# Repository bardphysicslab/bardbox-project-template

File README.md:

# bardbox-project-template

`bardbox-project-template` is the BardBox reference implementation and GitHub
template repo. New monitor projects should be created from this repo.

The canonical standards live in the separate `bardbox` repo. This template
implements those standards in working code: FastAPI backend, example driver,
dark BardBox dashboard, scripts, docs, and tests. Current firmware development
and proving live in [BardBox-Reference](https://github.com/bardphysicslab/BardBox-Reference/tree/main/software/firmware); this template intentionally contains no firmware copy.

## Decision history and contribution workflow

See the [implementation decision index](docs/DECISIONS.md), which links shared
platform reasoning back to BardBox. Use the issue and pull-request prompts with
the [shared development workflow](https://github.com/bardphysicslab/engineering-standards/blob/main/development-workflow.md).
Routine fixes stay brief; shared specifications are not copied into this template.

## Repo Roles

`bardbox` is the standards/specification repo.

`bardbox-project-template` is the reference implementation/template repo.

Workflow:

1. Protocol or UI rule changes are documented first in `bardbox`.
2. New capabilities are developed and proven in `BardBox-Reference` first,
   then verified reusable implementation, tests and build/configuration guidance
   are promoted into `bardbox-project-template` as tracked completion work
   ([TEMPLATE-PROVING-1](https://github.com/bardphysicslab/bardbox-project-template/issues/31#issuecomment-6281614801)).
   After promotion, Reference consumes the maintained implementation through the
   reviewed dependency boundary and retains its example configuration/demos.
3. New monitor repos are created from `bardbox-project-template`.
4. Existing monitor repos like GoLab, RKC, Solar, and CESH Air should be updated from the template standard when practical.
5. Project-specific repos should not invent protocol behavior unless it is promoted back into `bardbox` and `bardbox-project-template`.

Goal: one documented standard, one reference implementation, many project instances.

## What This Template Provides

- FastAPI Raspberry Pi app
- normalized reading API
- node freshness handling with `ok`, `stale`, `error`, and `node_unavailable`
- current node UID examples using `bb-<site>-<type>-<instance>`
- example driver contract
- CESH Air/RKC-derived BardBox landing and detail layouts
- reusable cards, status badges, foldouts, table, chart container, and mobile CSS
- exact lightweight `/health` endpoint and two-layer systemd/watchdog examples
- optional fail-closed read-only historical Data API
- canonical safe configuration synchronizer
- conditional verified-backup guidance and Tailscale deployment checklist
- root `bardbox.toml` project/service/config metadata for shared BardBox tooling
- isolated Python 3.12 development environment
- Dev Container and GitHub Actions test environment
- links to the current firmware proving home in Reference
- tests for stale/unavailable behavior

## Development Setup

Each BardBox repository owns its own Python environment. Do not run this project
from another BardBox repository's `.venv`; dependency leakage between repos can
hide or create failures that are not reproducible elsewhere.

From the repository root:

```bash
python3.12 -m venv .venv
source .venv/bin/activate
python -m pip install --upgrade pip
python -m pip install -r requirements-dev.txt
python -m pytest
```

Runtime dependencies remain in `requirements.txt`; development/test additions
are in `requirements-dev.txt`.

The repository includes a Python 3.12 Dev Container. With Docker running, validate
an identified committed revision in a fresh Linux container:

```bash
bash scripts/validate_container.sh HEAD
```

The runner prints the source commit, image identity/platform, interpreter and
resolved package versions. It builds from committed `.devcontainer` files and
streams a committed source archive into temporary container storage. Local edits,
untracked files and host virtual environments are excluded; commit intended changes
before using this as validation evidence. No host credentials, socket or hardware
are mounted. Dependencies require network access; fixture tests do not require
production devices. Containers are removed on exit; build images/cache remain for
reuse. This validates the native Docker architecture, not all CPU architectures.

CI runs the same command alongside isolated Python tests. The image tag and some
dependency ranges can resolve differently later; retain the printed evidence for
release reproducibility. Production Pi services continue to run natively/systemd.

A template change should pass both the repository's isolated local environment
and the clean Linux container before it is treated as a portable BardBox
foundation change.

## Quick Start

With the repository's `.venv` active:

```bash
uvicorn software.app.main:app --reload
```

Open [http://127.0.0.1:8000](http://127.0.0.1:8000). The landing page links to
the reference detail dashboard at `/monitor`.

Run commands from the repo root. The `software/app/` folder is a Python package;
do not `cd software/app` and run `uvicorn main:app`.

## First Customizations

1. Edit the root `bardbox.toml` project and service metadata.
2. Edit `software/app/config/app_config.example.json`.
3. Replace or add drivers under `software/app/drivers/`.
4. Follow [Reference firmware](https://github.com/bardphysicslab/BardBox-Reference/tree/main/software/firmware) for device development/proving; do not create a second firmware copy here.
5. Adjust dashboard labels and metric choices while preserving BardBox status/null behavior.
6. Add project-specific docs under `docs/`.

New node UIDs must use `bb-<site>-<type>-<instance>`, for example
`bb-prj-air-001`. Legacy `bb-0001` style IDs remain supported for existing
deployments but are deprecated.

During migration, add `legacy_uids` to a driver config to accept old
device-reported IDs while normalizing API/dashboard output to the canonical UID.
Historical logs are not rewritten.

## Firmware

Current firmware source, build definitions, host tests and demo receiver live in
[BardBox-Reference](https://github.com/bardphysicslab/BardBox-Reference/tree/main/software/firmware). The duplicate tree and firmware-only support were
[removed at Kornelis's request](https://github.com/bardphysicslab/bardbox-project-template/issues/36#issuecomment-6315599802); Template retains its server app and
normalized diagnostic receiver. Reference firmware is still under testing and
cleanup; this pointer does not claim a complete promoted firmware template.
Later reusable promotion/packaging is tracked in [#36](https://github.com/bardphysicslab/bardbox-project-template/issues/36).
Firmware uses VS Code + PlatformIO in Reference; no firmware build is run here.

## Repository Layout

```text
project/
├── bardbox.toml
├── .devcontainer/
├── .github/workflows/
├── software/
│   └── app/
├── hardware/
│   ├── ecad/
│   └── mcad/
├── data/
├── deploy/
├── docs/
├── scripts/
├── tests/
├── requirements.txt
├── requirements-dev.txt
└── README.md
```

## Standards Reference

Use `bardbox` as the specification repo for protocol, reading format, driver
boundaries, UI standards, channel names, and design decisions.
Network-uploading firmware must follow the canonical
[BardBox Web Node Protocol](https://github.com/bardphysicslab/bardbox/blob/main/docs/web-node-protocol.md);
this template keeps only a concise implementation checklist in
`docs/device-instructions.md`.

## BardBox Operations

After every source update, check whether the ignored live configuration needs
migration. Check mode performs no writes and exits non-zero if additions are
pending:

```bash
python3 scripts/sync_app_config.py --check
```

An informational preview is also available as either
`python3 scripts/sync_app_config.py` or
`python3 scripts/sync_app_config.py --dry-run`.

Apply the reviewed merge with:

```bash
python3 scripts/sync_app_config.py --write
```

The canonical BardBox synchronizer recursively adds new example fields while
preserving deployment values, secrets, and unknown local fields.
It matches nodes by UID, preserves local-only nodes, and does not automatically
create example-only nodes. Apply mode first creates a timestamped backup and
then atomically replaces the live file.

A deployment is ready to restart only when the check reports:

```text
Added keys: none
Added node fields: none
```

The deployment sequence is: pull, check, review/apply additions, check again,
restart, verify `/health`, and smoke-test the application.

`software/app/config/app_config.example.json` is sanitized and version
controlled. Copy it to ignored `software/app/config/app_config.json` for local
or production deployment values. Never place real secrets in the example.

## Availability Standard

Every deployed FastAPI/Uvicorn service needs both layers in `deploy/`:

- `Restart=always` and `RestartSec=5` recover an exited process;
- the one-minute watchdog checks `GET /health` and restarts after three
  consecutive failures, recovering a live but unresponsive process.

Adapt the generic paths, user, port, and service name before installation. Keep
the watchdog generic; do not add sensor or alert logic.

## Conditional Data API

The canonical router is included but disabled by default. It is appropriate only
when the deployment owns a clean `data/readings/` archive. Configure a dedicated
token only in ignored `app_config.json`:

```json
"data_api": { "token": "<dedicated read-only token>" }
```

An empty token fails closed. Authenticated consumers such as `bardbox-mcp` use
`GET /api/data/files` and `GET /api/data/files/{path}`. The API exposes only
CSV/CSV.GZ files and performs no writes, administration, or analysis. Remove or
leave the router disabled when a project has no suitable readings root.

## Optional Backup

Projects that retain and later prune local history should adapt the proven CESH
Air verified-manifest lifecycle. See `docs/backup-reference.md`. Stateless
projects should not add backup machinery.

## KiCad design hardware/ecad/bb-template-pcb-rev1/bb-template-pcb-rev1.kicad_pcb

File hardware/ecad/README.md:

# ECAD

Store version-controlled electronic design files, schematics, PCB layouts, and
related fabrication documentation for the project here.

The BardBox PCB template is forthcoming. The earlier draft
(`bb-template-pcb-rev1`) was removed from the active tree on October 20, 2026,
and remains in Git history.

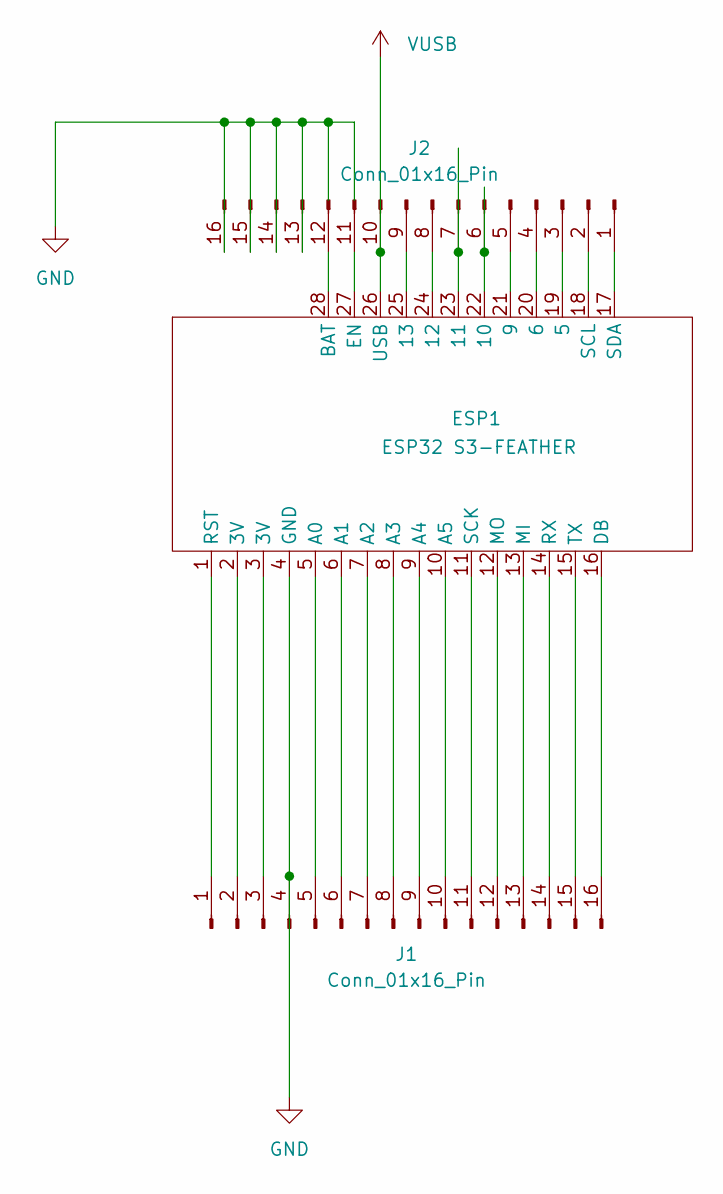
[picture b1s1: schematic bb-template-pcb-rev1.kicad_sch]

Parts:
ESP1: ESP32 S3-FEATHER
J1, J2: Conn_01x16_Pin; PinHeader_1x16_P2.54mm_Vertical

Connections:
GND: ESP1.4 (GND), J1.4, J2.13, J2.14, J2.15, J2.16
unnamed: ESP1.19 (5), J2.3
unnamed: ESP1.20 (6), J2.4
unnamed: ESP1.21 (9), J2.5
unnamed: ESP1.22 (10), J2.6
unnamed: ESP1.23 (11), J2.7
unnamed: ESP1.24 (12), J2.8
unnamed: ESP1.25 (13), J2.9
unnamed: ESP1.5 (A0), J1.5
unnamed: ESP1.6 (A1), J1.6
unnamed: ESP1.7 (A2), J1.7
unnamed: ESP1.8 (A3), J1.8
unnamed: ESP1.9 (A4), J1.9
unnamed: ESP1.10 (A5), J1.10
unnamed: ESP1.28 (BAT), J2.12
unnamed: ESP1.16 (DB), J1.16
unnamed: ESP1.27 (EN), J2.11
unnamed: ESP1.13 (MI), J1.13
unnamed: ESP1.12 (MO), J1.12
unnamed: ESP1.1 (RST), J1.1
unnamed: ESP1.14 (RX), J1.14
unnamed: ESP1.11 (SCK), J1.11
unnamed: ESP1.18 (SCL), J2.2
unnamed: ESP1.17 (SDA), J2.1
unnamed: ESP1.15 (TX), J1.15
unnamed: ESP1.2 (3V), J1.2
unnamed: ESP1.3 (3V), J1.3
VUSB: ESP1.26 (USB), J2.10

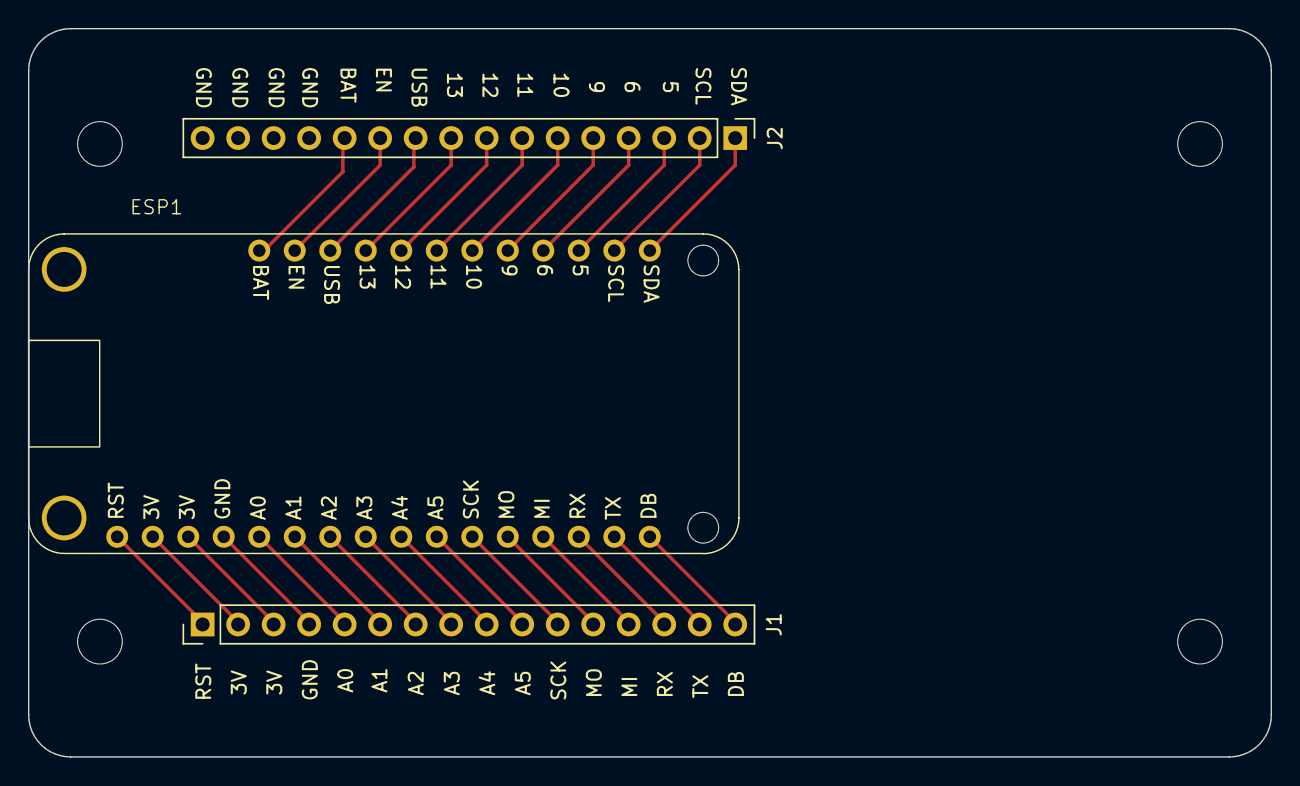
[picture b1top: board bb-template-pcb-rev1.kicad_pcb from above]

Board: 2 copper layers, 88.9 x 52.1 mm, 3 parts (0 on the bottom side), 28 nets.

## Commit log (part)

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2026-04-23 Initial BardBox project template
    - Skeleton FastAPI app with working dashboard
    - Standard header (Bard logo + title + clock)
    - Example driver implementing Bard Box contract
    - Config-driven structure
    - Repo layout aligned with Bard Box architecture
2026-04-23 fix: make template Python 3.9-safe and align local run instructions
2026-05-29 Align template with BardBox UID and freshness standards
